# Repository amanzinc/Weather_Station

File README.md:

# Weather Station PCB

This repository contains the design files and documentation for a **basic PCB** that integrates multiple environmental sensors and a solid-state relay, all controlled via an **ESP32 development board**.

## 📦 Components Integrated

* **DFRobot Gravity: PM2.5 Air Quality Sensor**
* **O₂ (Oxygen) Sensor**
* **SO₂ (Sulfur Dioxide) Sensor**
* **NO₂ (Nitrogen Dioxide) Sensor**
* **Solid-State Relay (SSR)**
* **ESP32 Development Board**

## 🛠️ Current Status

* ✅ Footprints created for all components
* ✅ Initial layout drafted in **KiCAD**
* 🧐 Currently verifying mechanical dimensions and clearances

## 📝 To-Do

* [ ] Complete PCB **routing**
* [ ] Improve **part file organization** for better reusability
* [ ] Add **Bill of Materials (BoM)**
* [ ] Document **sensor pinouts and power requirements**
* [ ] Test assembled PCB and update results

## 📁 Project Structure

```bash
project-root/
├── kicad_files/           # KiCAD project files
├── footprints/            # Custom footprints and symbols
├── datasheets/            # Sensor and component datasheets
├── images/                # Renders or screenshots of layout
├── docs/                  # Additional documentation
└── README.md              # This file
```

## 🤝 Contributions

Feel free to fork the repo and submit pull requests to help improve design replicability and documentation clarity.

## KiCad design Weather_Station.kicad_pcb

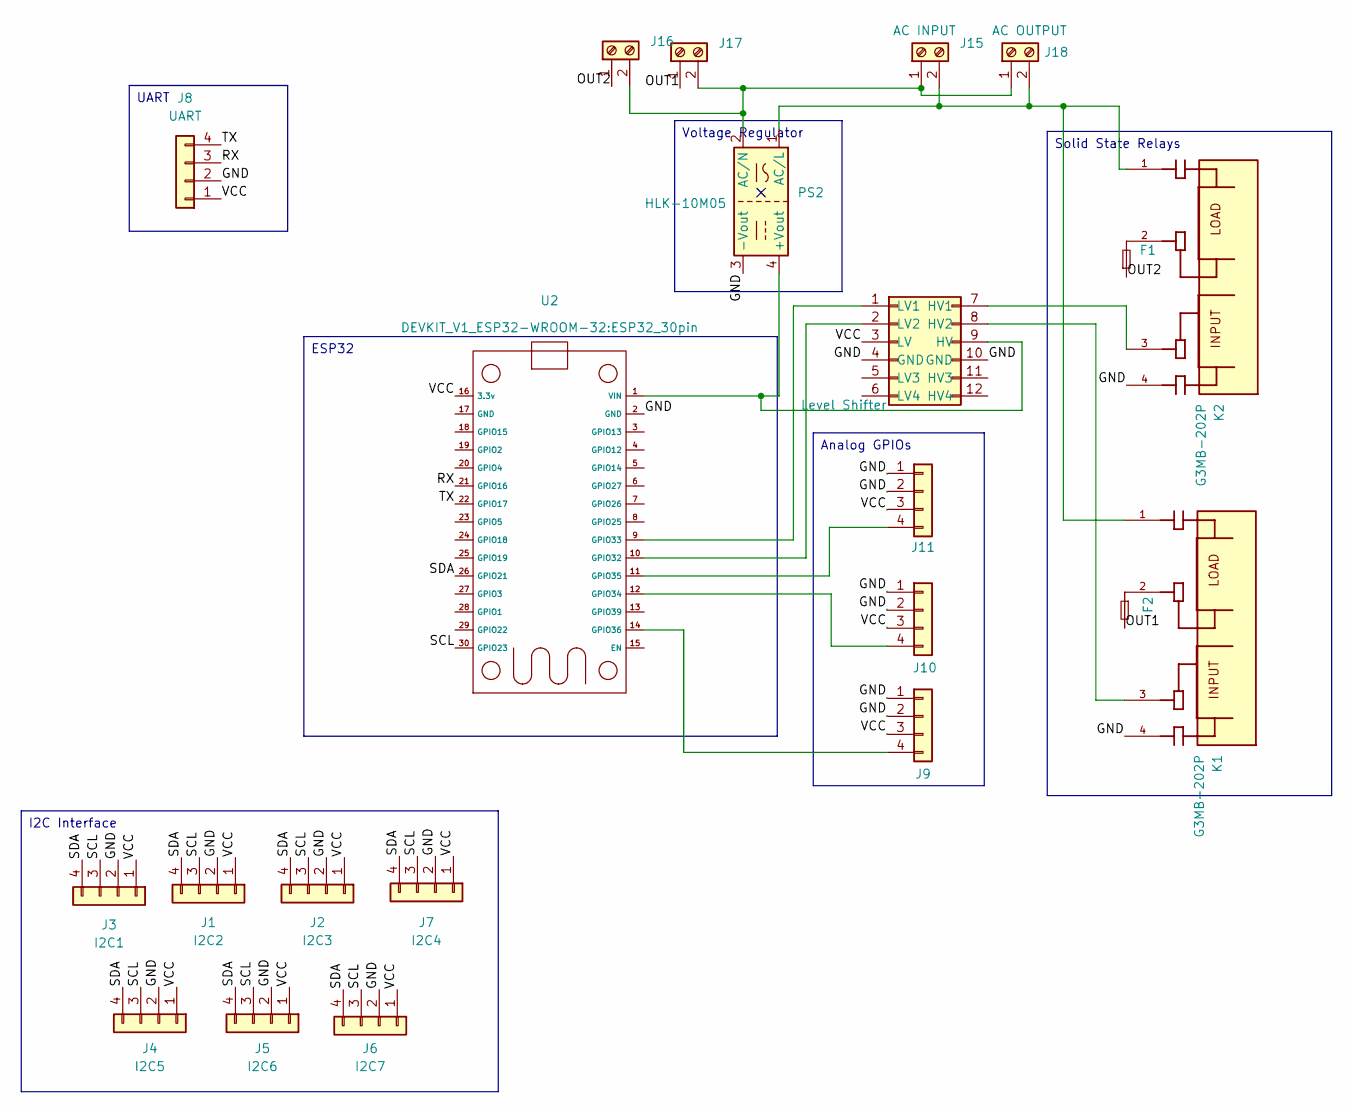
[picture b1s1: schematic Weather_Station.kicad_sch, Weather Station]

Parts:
F1, F2: Fuse_Small; Fuse_1206_3216Metric_Pad1.42x1.75mm_HandSolder
J1: I2C2; JST_XH_B4B-XH-A_1x04_P2.50mm_Vertical
J2: I2C3; JST_XH_B4B-XH-A_1x04_P2.50mm_Vertical
J3: I2C1; JST_XH_B4B-XH-A_1x04_P2.50mm_Vertical
J4: I2C5; JST_XH_B4B-XH-A_1x04_P2.50mm_Vertical
J5: I2C6; JST_XH_B4B-XH-A_1x04_P2.50mm_Vertical
J6: I2C7; JST_XH_B4B-XH-A_1x04_P2.50mm_Vertical
J7, J10, J11: I2C4; JST_XH_B4B-XH-A_1x04_P2.50mm_Vertical
J8: UART; JST_XH_B4B-XH-A_1x04_P2.50mm_Vertical
J9: JST_XH_B4B-XH-A_1x04_P2.50mm_Vertical
J14: Level Shifter; I2c Level Shifter
J15: AC INPUT; TerminalBlock_Phoenix_MKDS-1,5-2_1x02_P5.00mm_Horizontal
J16, J17: Screw_Terminal_01x02; TerminalBlock_Phoenix_MKDS-1,5-2_1x02_P5.00mm_Horizontal
J18: AC OUTPUT; TerminalBlock_Phoenix_MKDS-1,5-2_1x02_P5.00mm_Horizontal
K1, K2: G3MB-202P; RELAY_G3MB202PDC12; PARTREV J091-E1-1A
PS2: HLK-10M05; Converter_ACDC_Hi-Link_HLK-10Mxx
U2: ESP32_30pin

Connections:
/GND: J1.2, J2.2, J3.2, J4.2, J5.2, J6.2, J7.2, J8.2, J9.1, J9.2, J10.1, J10.2, J11.1, J11.2, J14.4 (GND), J14.10 (GND), K1.4, K2.4, PS2.3 (-Vout), U2.2 (GND)
/OUT1: F2.2, J17.1
/OUT2: F1.1, J16.1
/RX: J8.3, U2.21 (GPIO16)
/SCL: J1.3, J2.3, J3.3, J4.3, J5.3, J6.3, J7.3, U2.30 (GPIO23)
/SDA: J1.4, J2.4, J3.4, J4.4, J5.4, J6.4, J7.4, U2.26 (GPIO21)
/TX: J8.4, U2.22 (GPIO17)
/VCC: J1.1, J2.1, J3.1, J4.1, J5.1, J6.1, J7.1, J8.1, J9.3, J10.3, J11.3, J14.3 (LV), U2.16 (3.3v)
unnamed: F1.2, K2.2
unnamed: F2.1, K1.2
unnamed: J9.4, U2.14 (GPIO36)
unnamed: J10.4, U2.12 (GPIO34)
unnamed: J11.4, U2.11 (GPIO35)
unnamed: J14.7 (HV1), K2.3
unnamed: J14.8 (HV2), K1.3
unnamed: J14.9 (HV), PS2.4 (+Vout), U2.1 (VIN)
unnamed: J14.1 (LV1), U2.9 (GPIO33)
unnamed: J14.2 (LV2), U2.10 (GPIO32)
unnamed: J15.1, J16.2, J17.2, J18.1, PS2.2 (AC/N)
unnamed: J15.2, J18.2, K1.1, K2.1, PS2.1 (AC/L)

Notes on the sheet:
Solid State Relays
I2C Interface
UART
Analog GPIOs
Voltage Regulator
ESP32

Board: 2 copper layers, 22 parts (0 on the bottom side), 20 nets, no tracks yet.

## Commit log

2025-07-28 Initial Files
